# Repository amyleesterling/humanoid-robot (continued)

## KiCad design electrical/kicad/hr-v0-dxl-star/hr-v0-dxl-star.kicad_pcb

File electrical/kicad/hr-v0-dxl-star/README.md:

# HR-V0 DYNAMIXEL star injection DXL-STAR-P0.1

**PRELIMINARY - NOT APPROVED FOR FABRICATION OR ENERGIZATION**

This native KiCad candidate implements one fixed central branch-isolating board:

- `JC1` is JST `B3B-EH-A`; pins 1/3 carry GND/DATA and pin 2 has no PCB net or route.
- `JP1`-`JP3` are JST `B2P-VH` protected branch inputs; project pin 1 is VDD and pin 2 return.
- `JA1`-`JA3` are JST `B3B-EH-A` actuator outputs using standard ROBOTIS TTL pin order.
- `J1_VDD`, `J2_VDD`, and `J3_VDD` are routed separately and never join.
- `DXL_TTL_DATA` and `ACT_0V_PE_BONDED` are common by design.

The source contains no released cable lengths, branch conductors, fuse ratings, assembly outputs, Gerber/drill package or permission to fabricate. U2D2 pin-2 omission, VDD isolation, grounding, star-bus signal integrity, connector temperature, no-backfeed and fault behavior require physical evidence and qualified review.

Generate with KiCad 10 bundled Python:

`"C:\Program Files\KiCad\10.0\bin\python.exe" tools/generate_hr_v0_dxl_star.py`

Then run `tools/check_hr_v0_dxl_star.py` with the same interpreter. ERC/DRC prove encoded connectivity only.

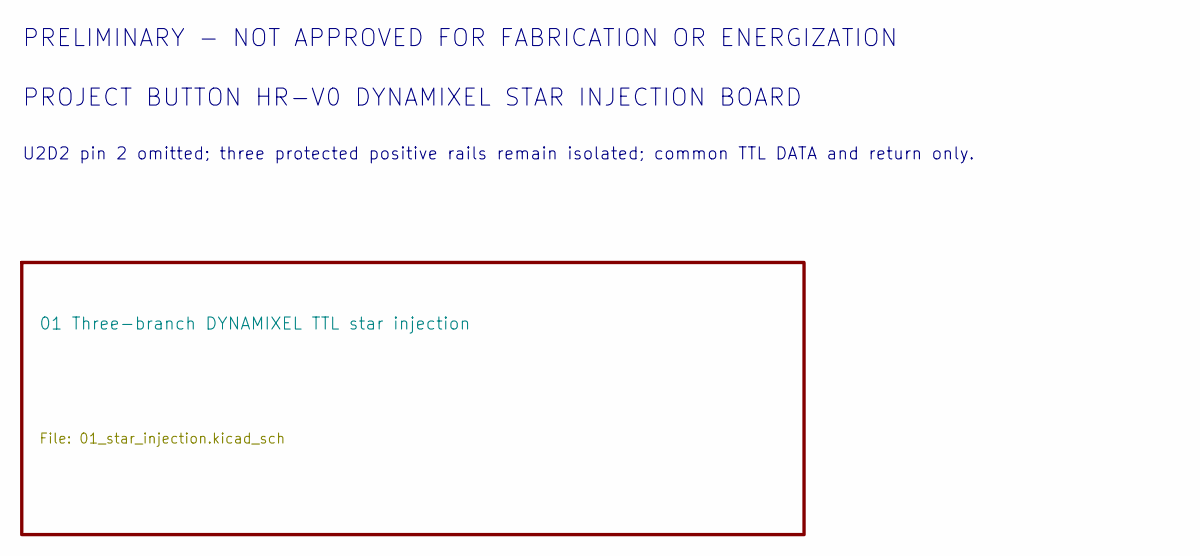
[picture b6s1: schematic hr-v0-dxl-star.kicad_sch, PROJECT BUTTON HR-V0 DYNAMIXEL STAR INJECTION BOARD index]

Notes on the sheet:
PRELIMINARY - NOT APPROVED FOR FABRICATION OR ENERGIZATION
PROJECT BUTTON HR-V0 DYNAMIXEL STAR INJECTION BOARD
U2D2 pin 2 omitted; three protected positive rails remain isolated; common TTL DATA and return only.

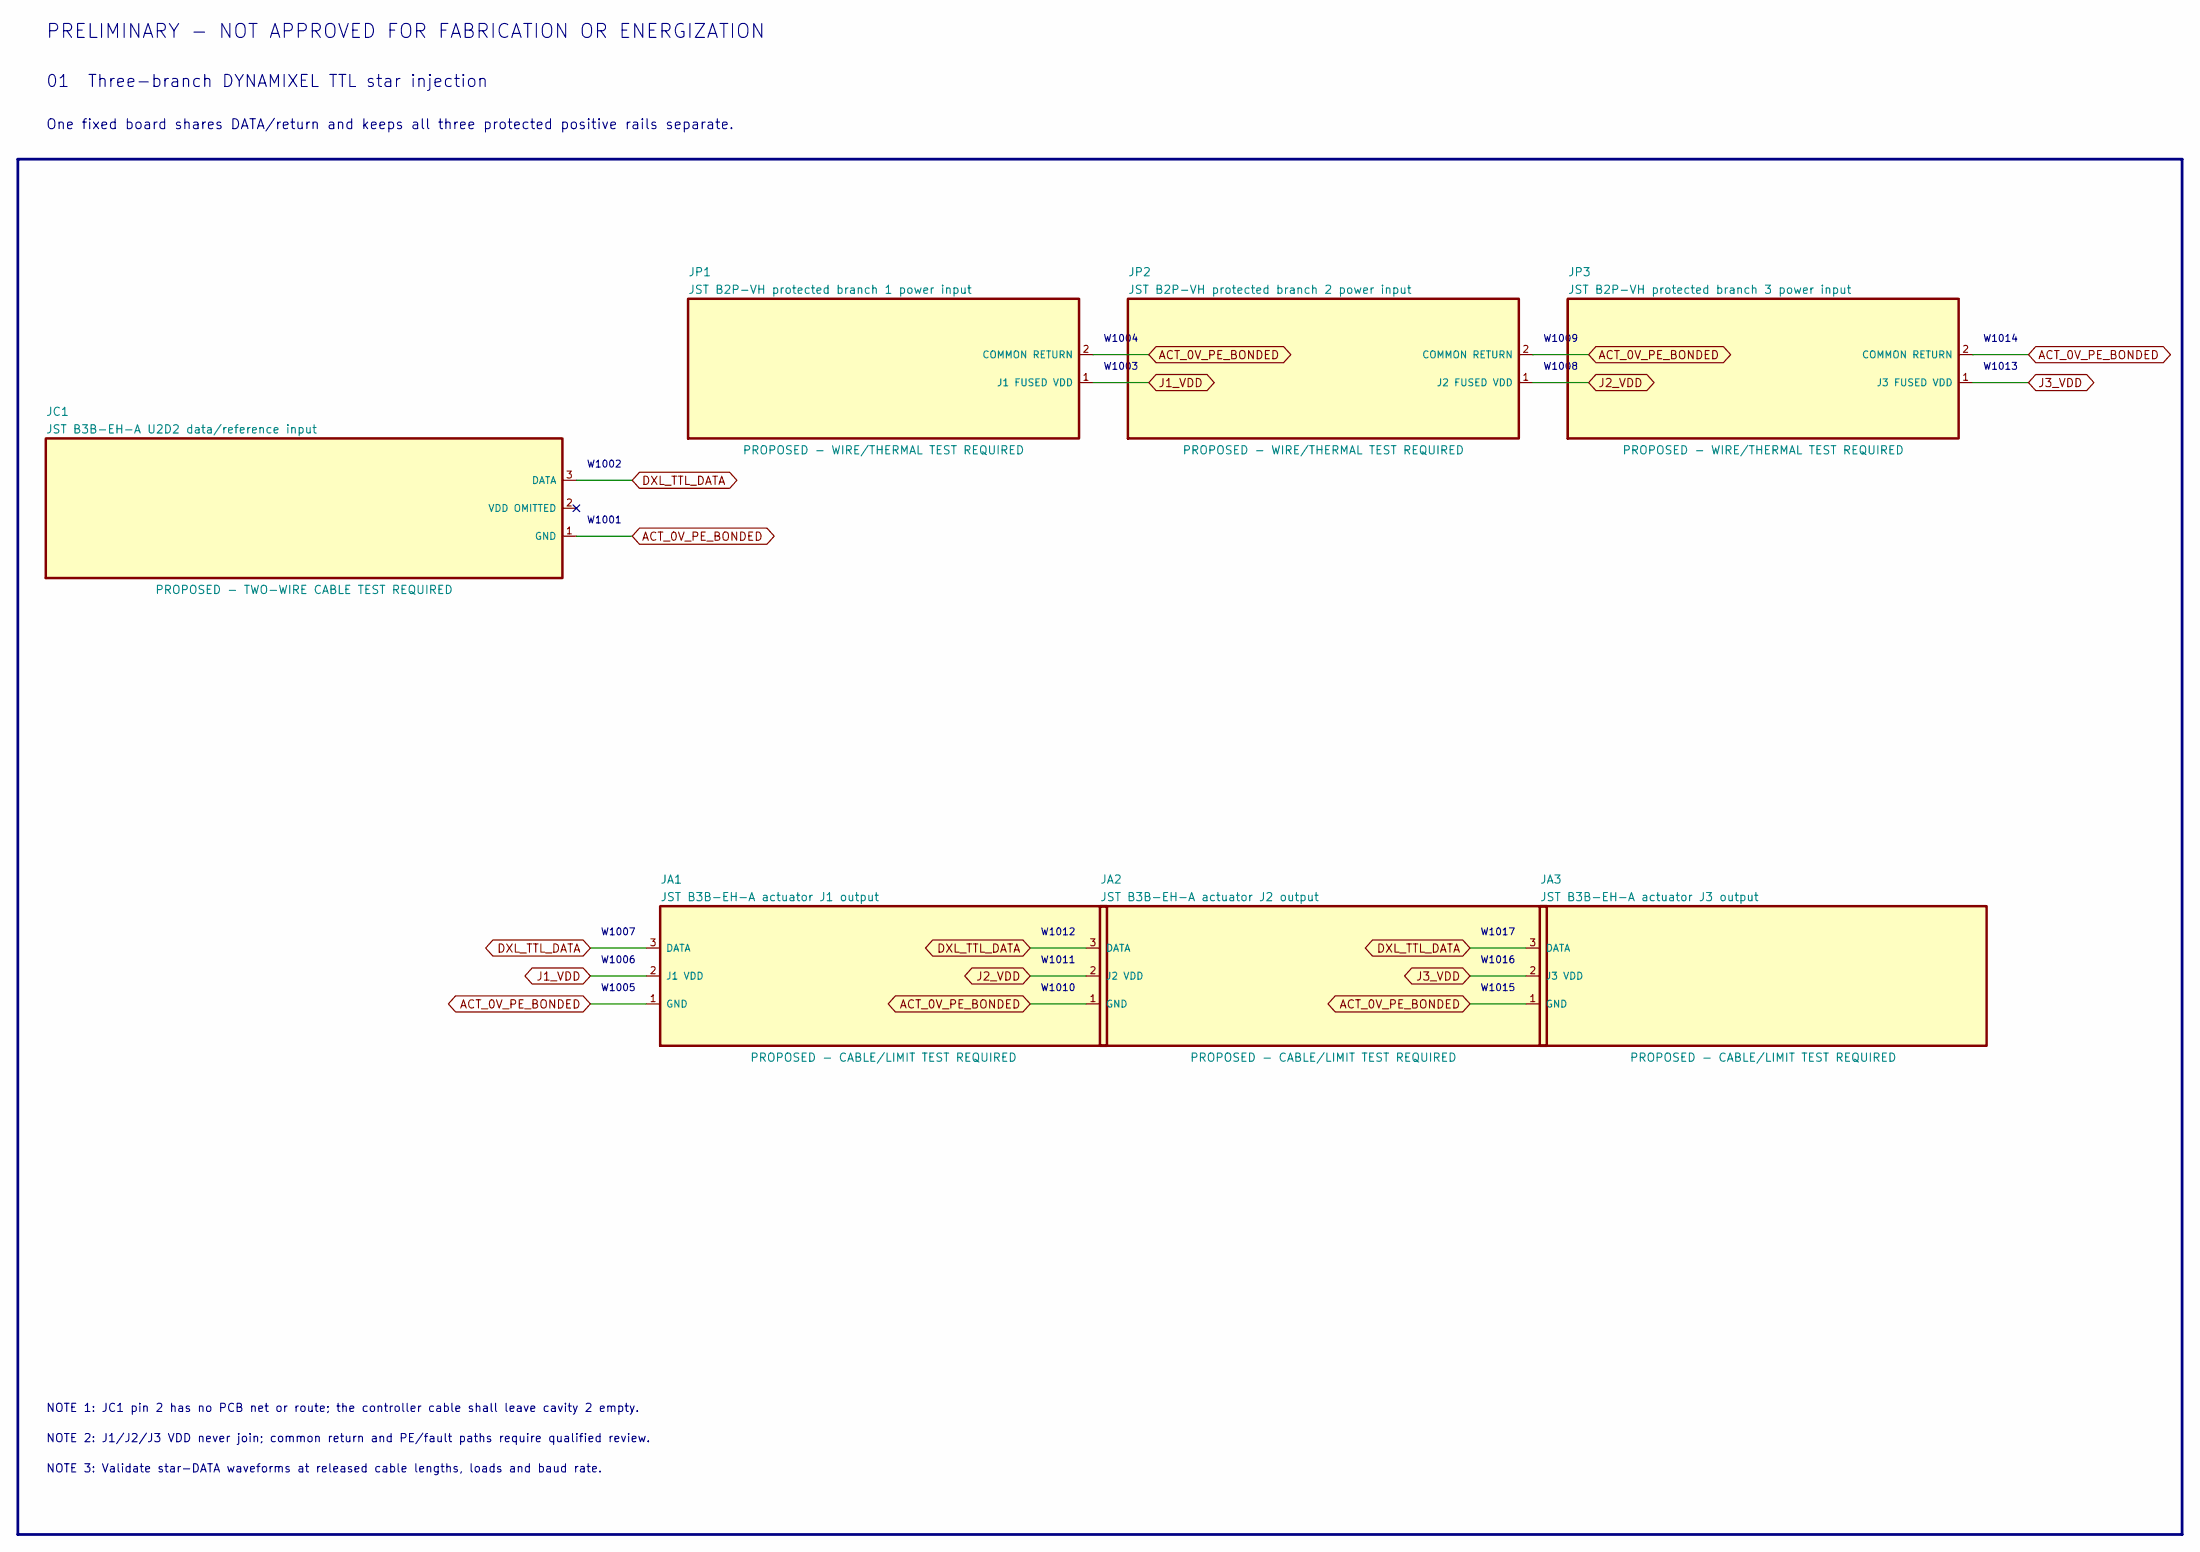
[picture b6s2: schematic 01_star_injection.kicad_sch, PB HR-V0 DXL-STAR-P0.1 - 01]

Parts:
JA1: JST B3B-EH-A actuator J1 output; JST_EH_B3B-EH-A_1x03_P2.50mm_Vertical
JA2: JST B3B-EH-A actuator J2 output; JST_EH_B3B-EH-A_1x03_P2.50mm_Vertical
JA3: JST B3B-EH-A actuator J3 output; JST_EH_B3B-EH-A_1x03_P2.50mm_Vertical
JC1: JST B3B-EH-A U2D2 data/reference input; JST_EH_B3B-EH-A_1x03_P2.50mm_Vertical
JP1: JST B2P-VH protected branch 1 power input; JST_VH_B2P-VH_1x02_P3.96mm_Vertical
JP2: JST B2P-VH protected branch 2 power input; JST_VH_B2P-VH_1x02_P3.96mm_Vertical
JP3: JST B2P-VH protected branch 3 power input; JST_VH_B2P-VH_1x02_P3.96mm_Vertical

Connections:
ACT_0V_PE_BONDED: JA1.1 (GND), JA2.1 (GND), JA3.1 (GND), JC1.1 (GND), JP1.2 (COMMON RETURN), JP2.2 (COMMON RETURN), JP3.2 (COMMON RETURN)
DXL_TTL_DATA: JA1.3 (DATA), JA2.3 (DATA), JA3.3 (DATA), JC1.3 (DATA)
J1_VDD: JA1.2 (J1 VDD), JP1.1 (J1 FUSED VDD)
J2_VDD: JA2.2 (J2 VDD), JP2.1 (J2 FUSED VDD)
J3_VDD: JA3.2 (J3 VDD), JP3.1 (J3 FUSED VDD)

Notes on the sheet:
PRELIMINARY - NOT APPROVED FOR FABRICATION OR ENERGIZATION
01 Three-branch DYNAMIXEL TTL star injection
One fixed board shares DATA/return and keeps all three protected positive rails separate.
W1001
W1002
W1003
W1004
W1005
W1006
W1007
W1008
W1009
W1010
W1011
W1012
W1013
W1014
W1015
W1016
W1017
NOTE 1: JC1 pin 2 has no PCB net or route; the controller cable shall leave cavity 2 empty.
NOTE 2: J1/J2/J3 VDD never join; common return and PE/fault paths require qualified review.
NOTE 3: Validate star-DATA waveforms at released cable lengths, loads and baud rate.

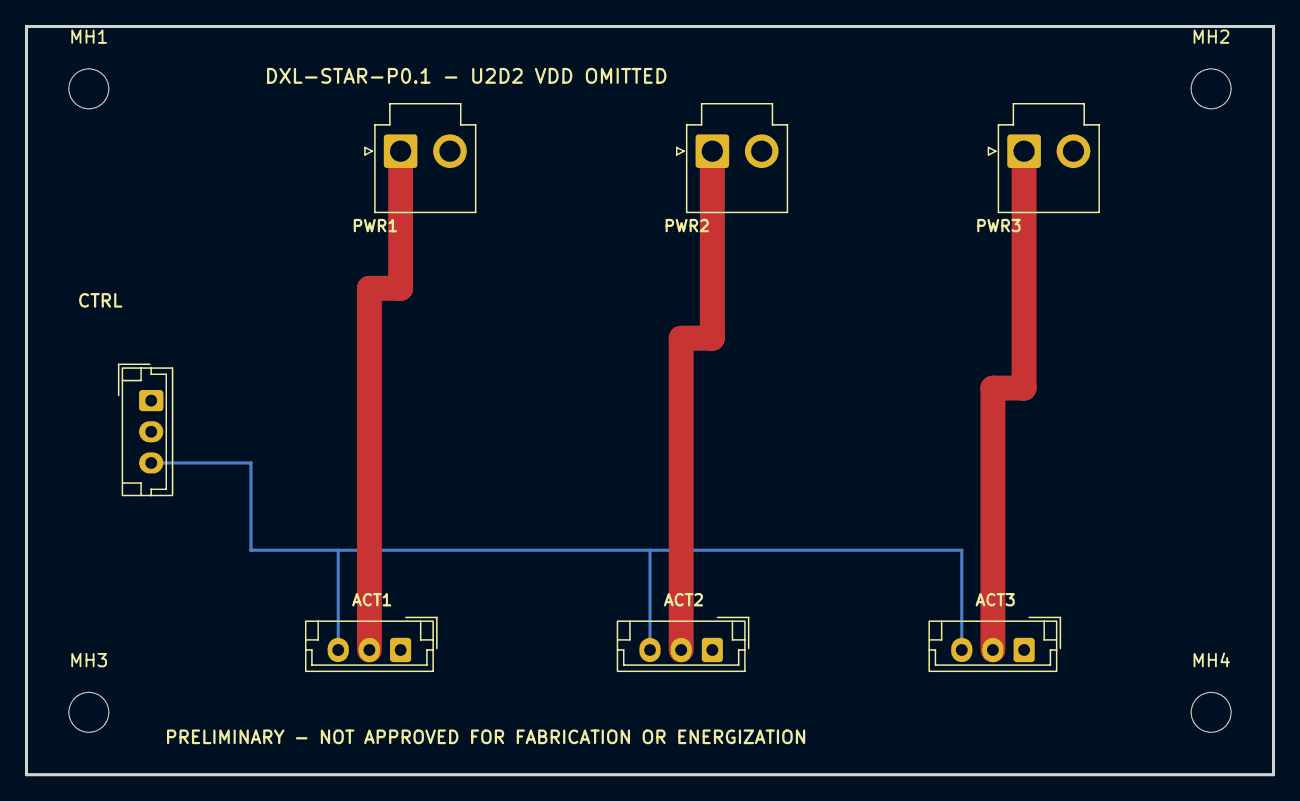
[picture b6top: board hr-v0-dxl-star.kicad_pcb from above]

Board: 2 copper layers, 100.0 x 60.0 mm, 11 parts (0 on the bottom side), 5 nets.

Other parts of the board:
MH1, MH2, MH3, MH4: M3 BOARD-ONLY - ENCLOSURE/MOUNTING SELECTION OPEN; MountingHole_3.2mm_M3

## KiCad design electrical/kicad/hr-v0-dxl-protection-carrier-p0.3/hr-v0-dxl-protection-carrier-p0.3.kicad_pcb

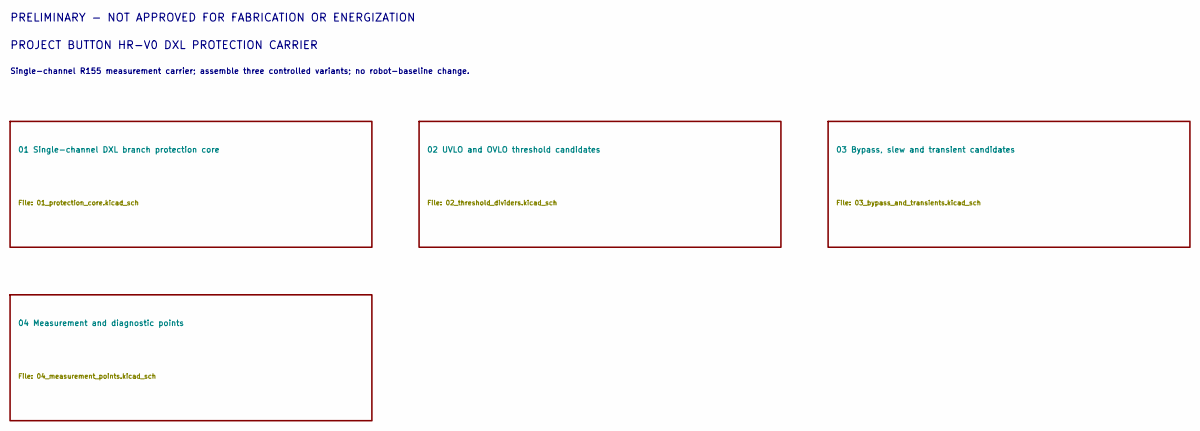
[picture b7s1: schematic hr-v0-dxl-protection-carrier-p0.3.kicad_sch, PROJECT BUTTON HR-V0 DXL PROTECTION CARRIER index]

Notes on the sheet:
PRELIMINARY - NOT APPROVED FOR FABRICATION OR ENERGIZATION
PROJECT BUTTON HR-V0 DXL PROTECTION CARRIER
Single-channel R155 measurement carrier; assemble three controlled variants; no robot-baseline change.

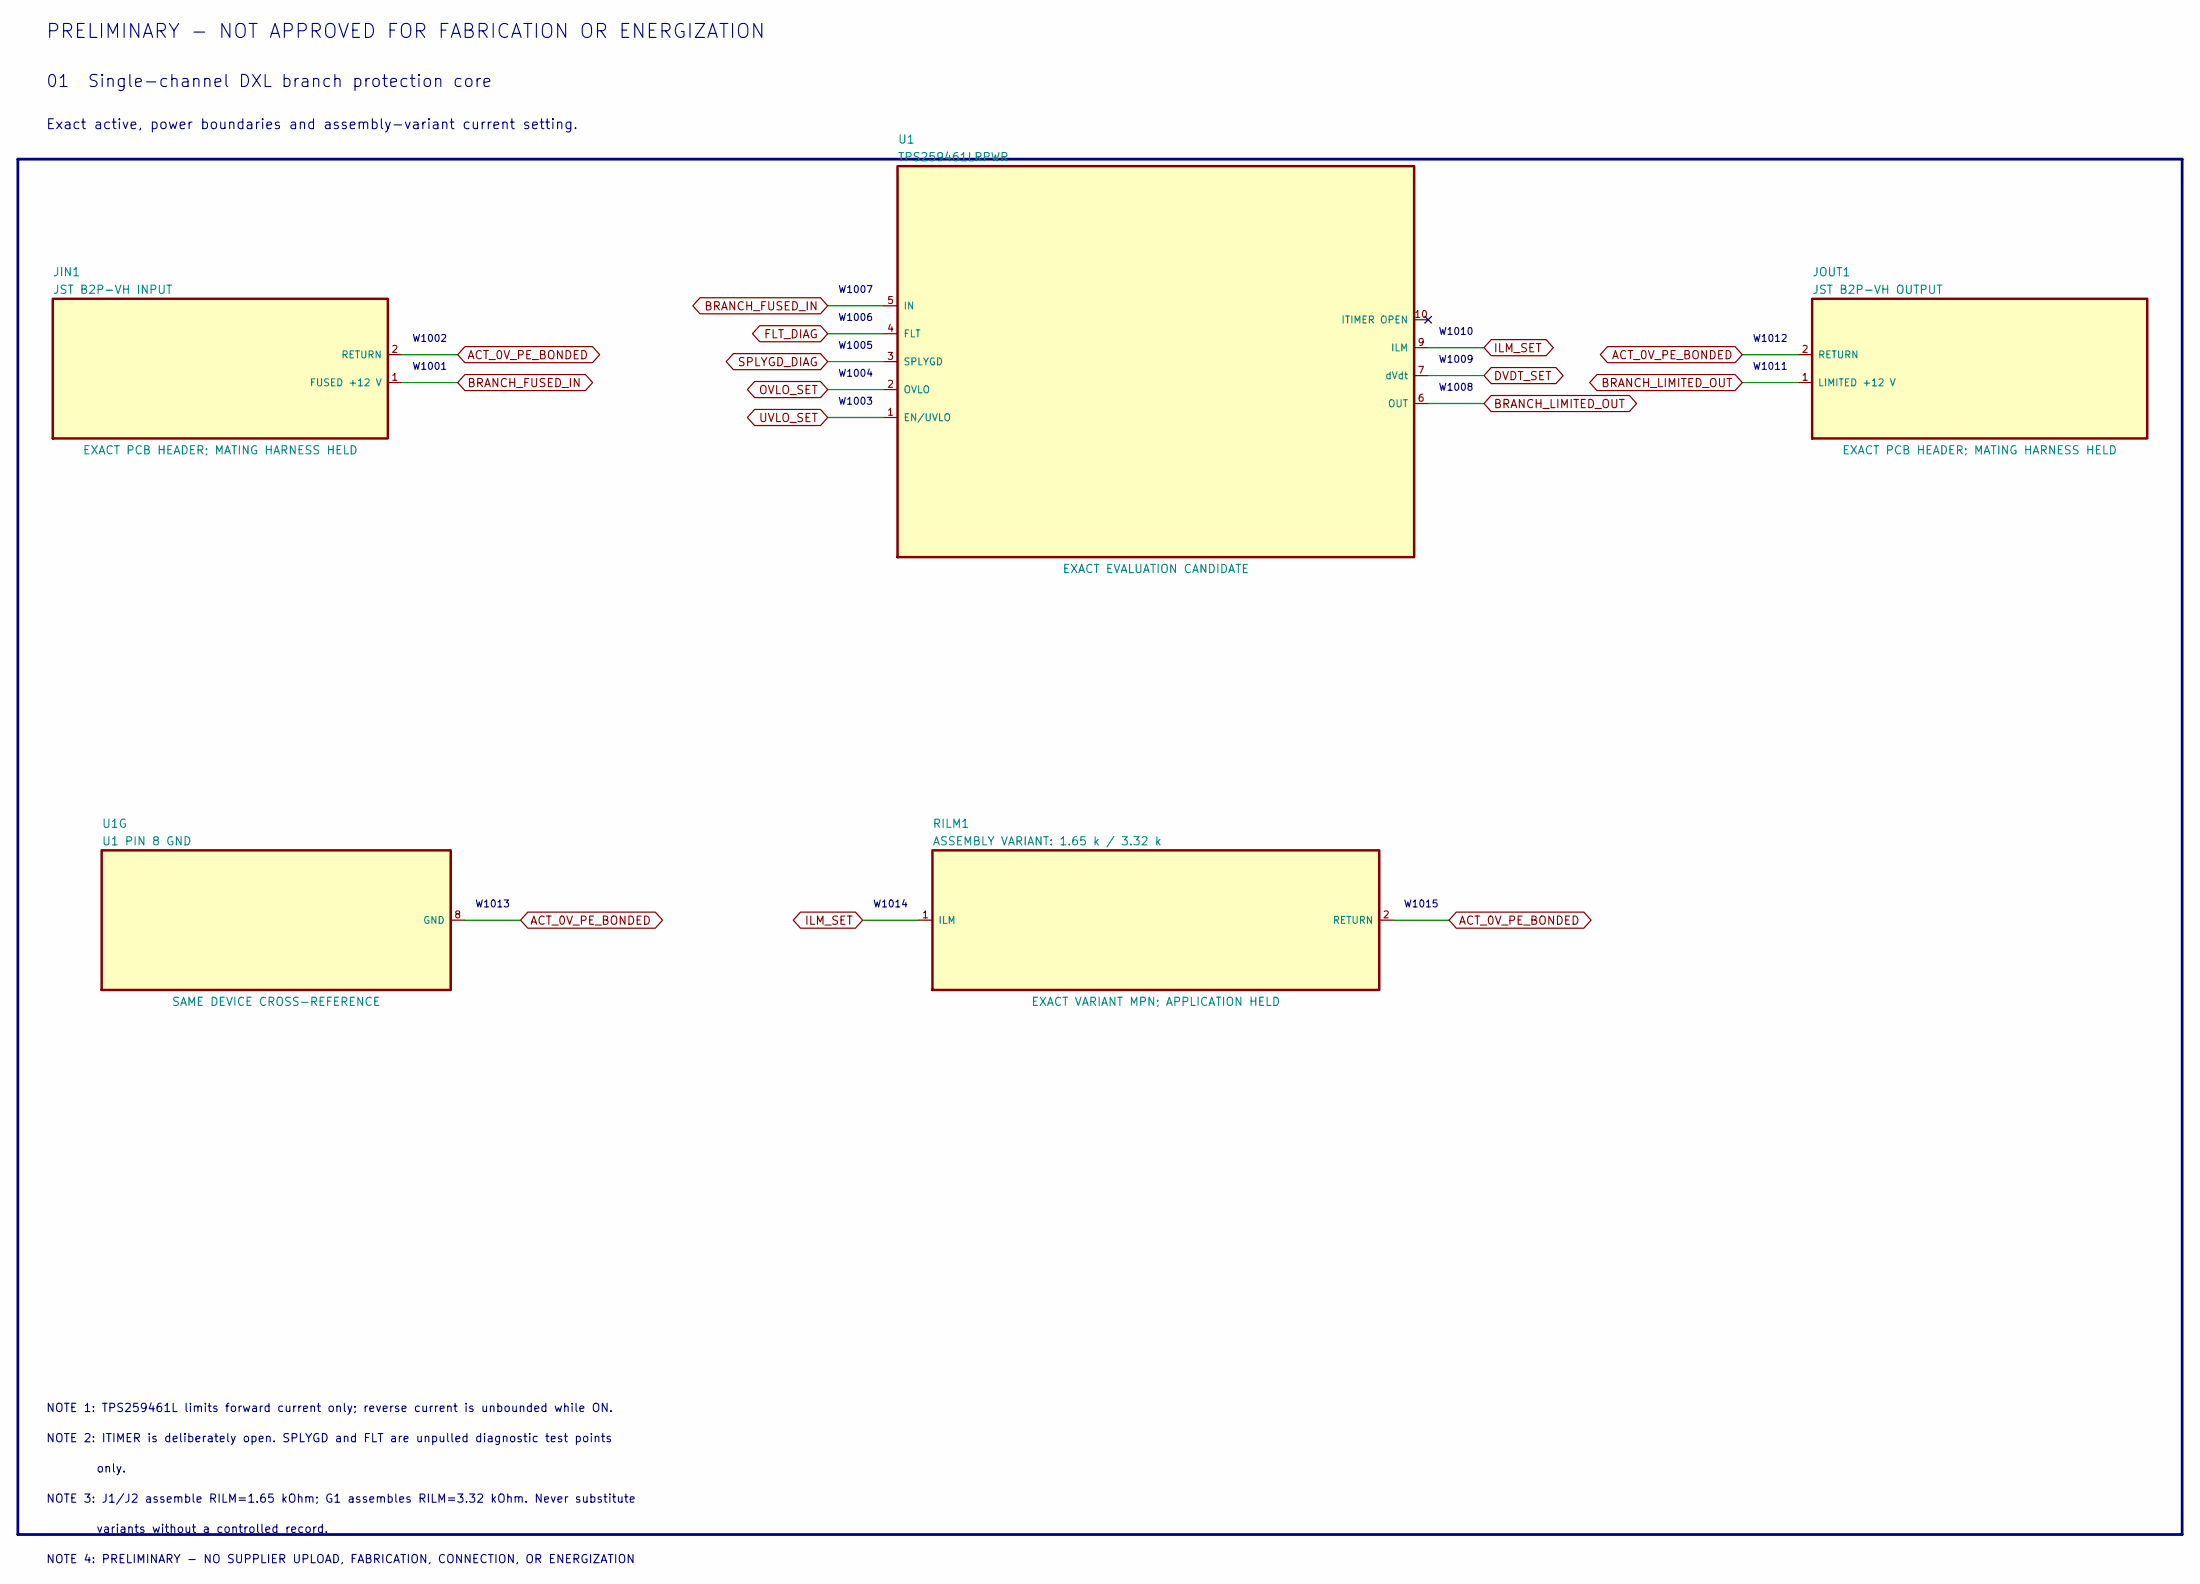
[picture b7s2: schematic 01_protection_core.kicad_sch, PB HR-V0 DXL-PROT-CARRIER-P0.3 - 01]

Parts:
JIN1: JST B2P-VH INPUT; JST_VH_B2P-VH_1x02_P3.96mm_Vertical
JOUT1: JST B2P-VH OUTPUT; JST_VH_B2P-VH_1x02_P3.96mm_Vertical
RILM1: ASSEMBLY VARIANT: 1.65 k / 3.32 k; R_0603_1608Metric
U1: TPS259461LRPWR; TI_RPW0010A_HotRodQFN_2x2mm_P0.45mm_TI4225183A_P02
U1G: U1 PIN 8 GND; TI_RPW0010A_HotRodQFN_2x2mm_P0.45mm_TI4225183A_P02

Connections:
ACT_0V_PE_BONDED: JIN1.2 (RETURN), JOUT1.2 (RETURN), RILM1.2 (RETURN), U1.8, U1G.8; also elsewhere on the board
BRANCH_FUSED_IN: JIN1.1 (FUSED +12 V), U1.5 (IN); also elsewhere on the board
BRANCH_LIMITED_OUT: JOUT1.1 (LIMITED +12 V), U1.6 (OUT); also elsewhere on the board
DVDT_SET: U1.7 (dVdt); also elsewhere on the board
FLT_DIAG: U1.4 (FLT); also elsewhere on the board
ILM_SET: RILM1.1 (ILM), U1.9 (ILM); also elsewhere on the board
OVLO_SET: U1.2 (OVLO); also elsewhere on the board
SPLYGD_DIAG: U1.3 (SPLYGD); also elsewhere on the board
UVLO_SET: U1.1 (EN/UVLO); also elsewhere on the board

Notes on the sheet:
PRELIMINARY - NOT APPROVED FOR FABRICATION OR ENERGIZATION
01 Single-channel DXL branch protection core
Exact active, power boundaries and assembly-variant current setting.
W1001
W1002
W1003
W1004
W1005
W1006
W1007
W1008
W1009
W1010
W1011
W1012
W1013
W1014
W1015
NOTE 1: TPS259461L limits forward current only; reverse current is unbounded while ON.
NOTE 2: ITIMER is deliberately open. SPLYGD and FLT are unpulled diagnostic test points
only.
NOTE 3: J1/J2 assemble RILM=1.65 kOhm; G1 assembles RILM=3.32 kOhm. Never substitute
variants without a controlled record.
NOTE 4: PRELIMINARY - NO SUPPLIER UPLOAD, FABRICATION, CONNECTION, OR ENERGIZATION

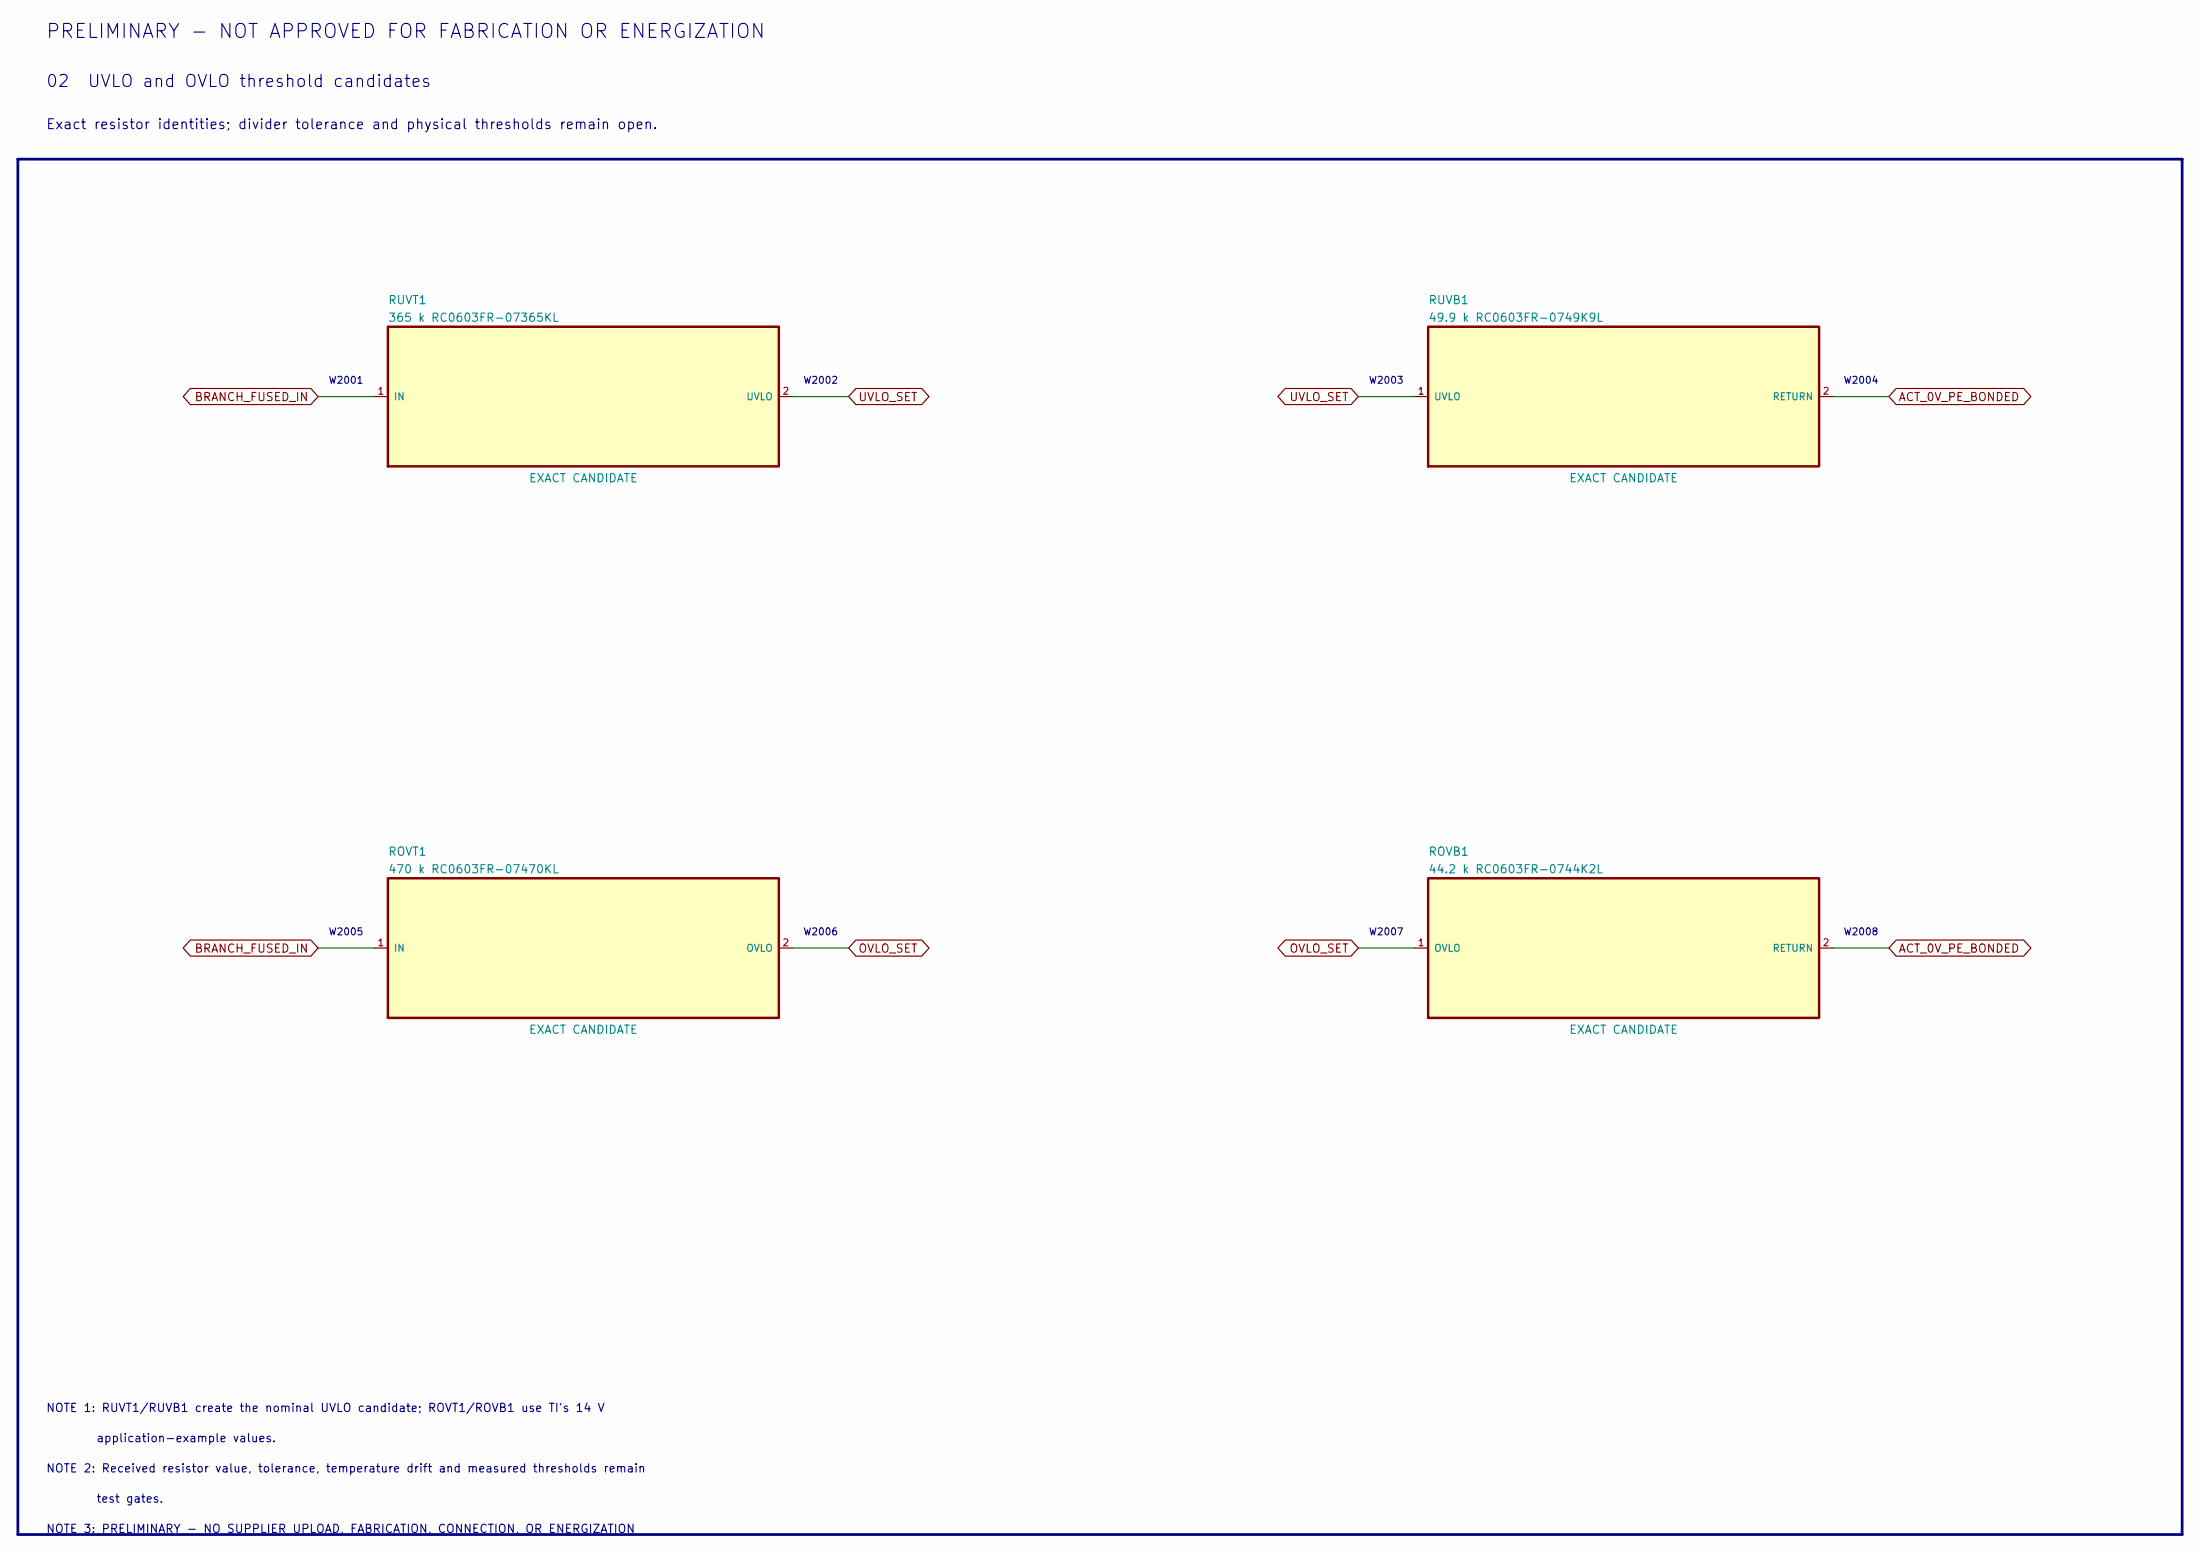
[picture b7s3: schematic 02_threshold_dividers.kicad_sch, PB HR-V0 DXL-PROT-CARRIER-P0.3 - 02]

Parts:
ROVB1: 44.2 k RC0603FR-0744K2L; R_0603_1608Metric
ROVT1: 470 k RC0603FR-07470KL; R_0603_1608Metric
RUVB1: 49.9 k RC0603FR-0749K9L; R_0603_1608Metric
RUVT1: 365 k RC0603FR-07365KL; R_0603_1608Metric

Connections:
ACT_0V_PE_BONDED: ROVB1.2 (RETURN), RUVB1.2 (RETURN); also elsewhere on the board
BRANCH_FUSED_IN: ROVT1.1 (IN), RUVT1.1 (IN); also elsewhere on the board
OVLO_SET: ROVB1.1 (OVLO), ROVT1.2 (OVLO); also elsewhere on the board
UVLO_SET: RUVB1.1 (UVLO), RUVT1.2 (UVLO); also elsewhere on the board

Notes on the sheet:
PRELIMINARY - NOT APPROVED FOR FABRICATION OR ENERGIZATION
02 UVLO and OVLO threshold candidates
Exact resistor identities; divider tolerance and physical thresholds remain open.
W2001
W2002
W2003
W2004
W2005
W2006
W2007
W2008
NOTE 1: RUVT1/RUVB1 create the nominal UVLO candidate; ROVT1/ROVB1 use TI's 14 V
application-example values.
NOTE 2: Received resistor value, tolerance, temperature drift and measured thresholds remain
test gates.
NOTE 3: PRELIMINARY - NO SUPPLIER UPLOAD, FABRICATION, CONNECTION, OR ENERGIZATION

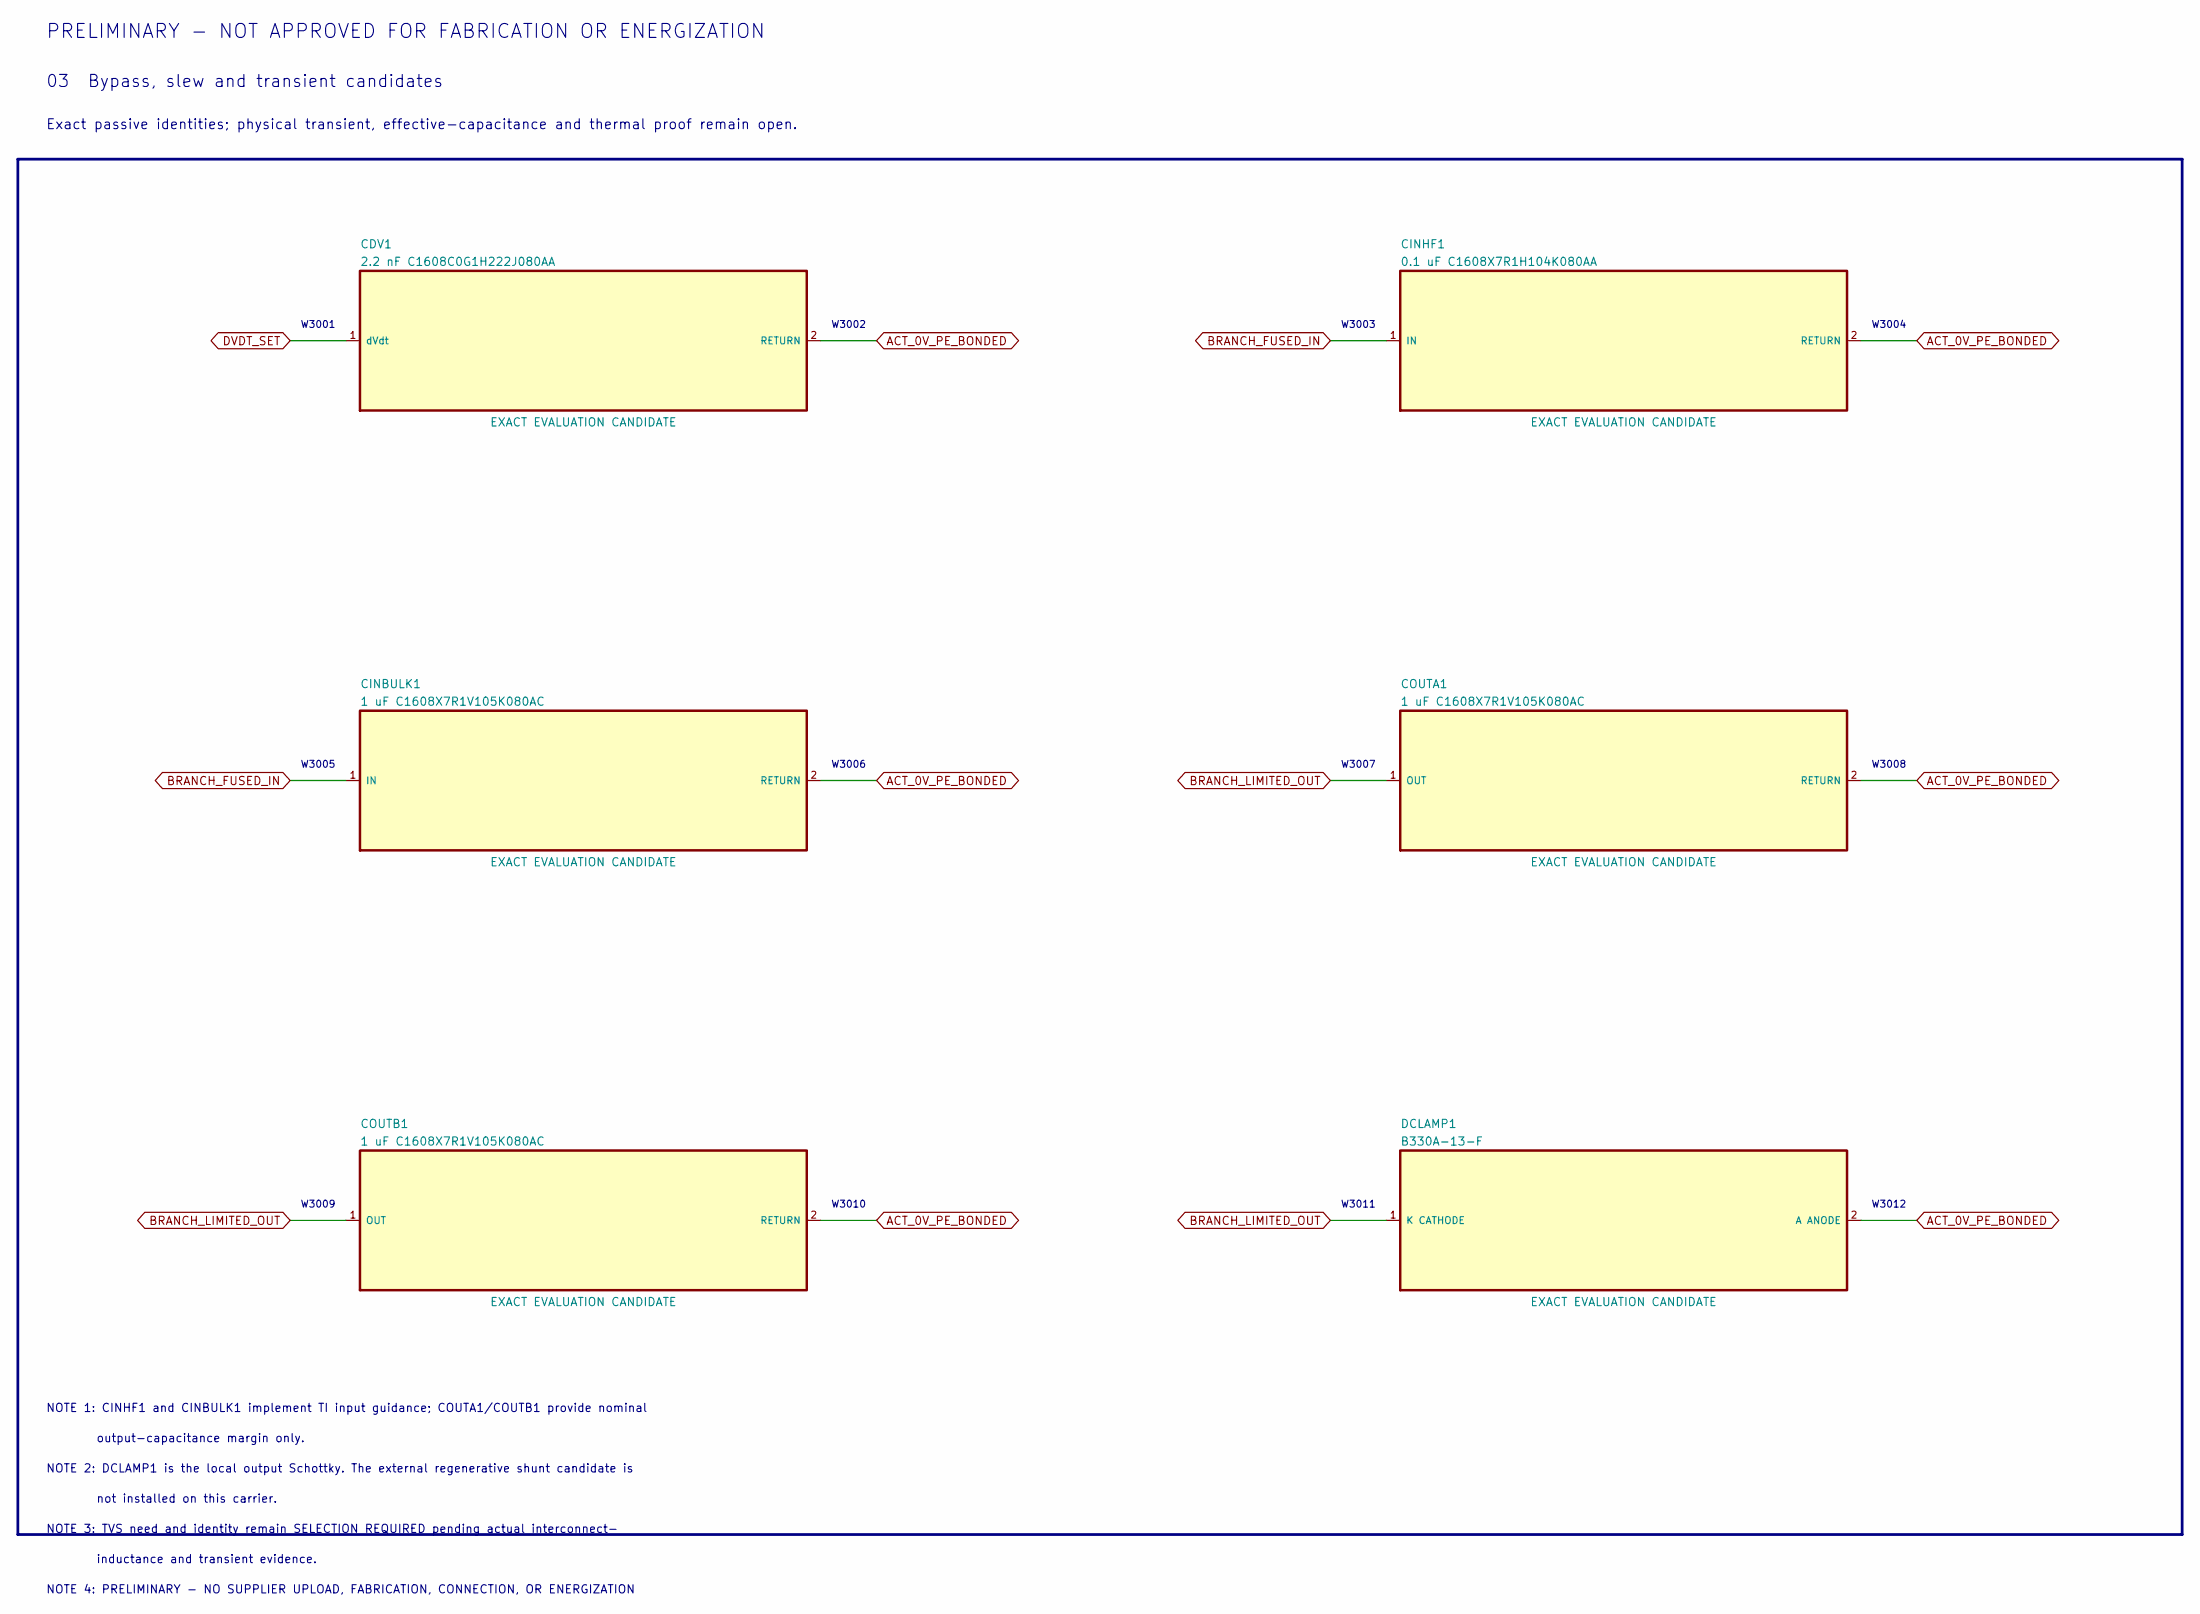
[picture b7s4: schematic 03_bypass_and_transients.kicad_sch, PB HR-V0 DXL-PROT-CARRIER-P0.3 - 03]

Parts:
CDV1: 2.2 nF C1608C0G1H222J080AA; C_0603_1608Metric
CINBULK1: 1 uF C1608X7R1V105K080AC; C_0603_1608Metric
CINHF1: 0.1 uF C1608X7R1H104K080AA; C_0603_1608Metric
COUTA1: 1 uF C1608X7R1V105K080AC; C_0603_1608Metric
COUTB1: 1 uF C1608X7R1V105K080AC; C_0603_1608Metric
DCLAMP1: B330A-13-F; D_SMA

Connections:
ACT_0V_PE_BONDED: CDV1.2 (RETURN), CINBULK1.2 (RETURN), CINHF1.2 (RETURN), COUTA1.2 (RETURN), COUTB1.2 (RETURN), DCLAMP1.2 (A ANODE); also elsewhere on the board
BRANCH_FUSED_IN: CINBULK1.1 (IN), CINHF1.1 (IN); also elsewhere on the board
BRANCH_LIMITED_OUT: COUTA1.1 (OUT), COUTB1.1 (OUT), DCLAMP1.1 (K CATHODE); also elsewhere on the board
DVDT_SET: CDV1.1 (dVdt); also elsewhere on the board

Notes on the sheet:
PRELIMINARY - NOT APPROVED FOR FABRICATION OR ENERGIZATION
03 Bypass, slew and transient candidates
Exact passive identities; physical transient, effective-capacitance and thermal proof remain open.
W3001
W3002
W3003
W3004
W3005
W3006
W3007
W3008
W3009
W3010
W3011
W3012
NOTE 1: CINHF1 and CINBULK1 implement TI input guidance; COUTA1/COUTB1 provide nominal
output-capacitance margin only.
NOTE 2: DCLAMP1 is the local output Schottky. The external regenerative shunt candidate is
not installed on this carrier.
NOTE 3: TVS need and identity remain SELECTION REQUIRED pending actual interconnect-
inductance and transient evidence.
NOTE 4: PRELIMINARY - NO SUPPLIER UPLOAD, FABRICATION, CONNECTION, OR ENERGIZATION
